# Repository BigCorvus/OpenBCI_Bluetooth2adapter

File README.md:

# OpenBCI_Bluetooth2adapter

Eagle files for an adapter board for the OpenBCI 32bit V3 board (Cyton) that enables higher data/sampling rates and eliminates the need for a USB dongle. Reliable operation is possible with 500Hz and 8 channels or 250Hz and 16 Channels. The OpenBCI GUI 2.0 is able to keep up with that.
The bluetooth module used is the common HC-05. Programming the board is still accomplished via dongle/RFduino.

In order for this board to work you have to implement WinslowStrong's changes in firmware (https://github.com/WinslowStrong/OpenBCI_Wired_USB) and you have to set up a baud rate of 230400baud on your bluetooth module (this is the highest rate I've been able to acheive reliably with the HC05). 
I've modified my Cyton board by putting the RFduino module on headers so that it can be removed after flashing the modified firmware. 

A solder jumper is included on the bottom side of the board to enter programming mode. You can short it temporarily using some metal object. In command mode (the LED is blinking slowly) you have to set a baud rate of 38400baud 8N1 and send after each command \r\n. If you enter AT the module should respond with OK.
To set the baud rate just enter AT+UART=230400,0,0 and to set the name type in AT+NAME=OpenBCI32 or whatever name you like. 

Edit: I also created a version for the RN42 module (http://www.digikey.com/product-detail/en/microchip-technology/RN42-I-RM630/RN42-I-RM630-ND/6009311) which can acheive speeds at up to 460800 baud in the system.

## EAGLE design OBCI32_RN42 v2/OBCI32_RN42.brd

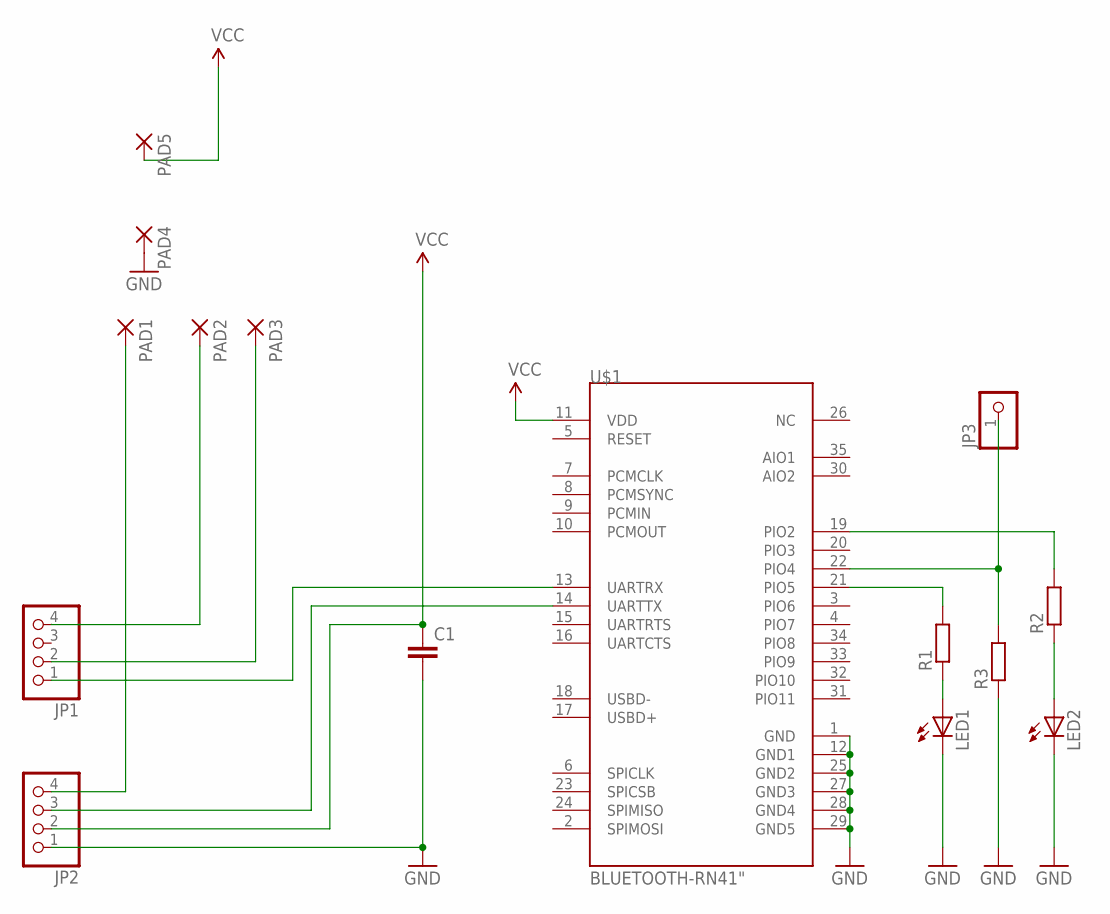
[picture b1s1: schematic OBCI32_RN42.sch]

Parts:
C1: C-EUC0805; C0805
JP1, JP2: PINHD-1X4; 1X04
JP3: PINHD-1X1; 1X01
LED1, LED2: LEDCHIP-LED0805; CHIP-LED0805
PAD1, PAD2, PAD3, PAD4, PAD5: SMD2; SMD1,27-2,54
R1, R2, R3: R-EU_R0603; R0603
U$1: BLUETOOTH-RN41"; RN41

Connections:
GND: C1.2, JP2.1, LED1.C, LED2.C, PAD4.1, R3.1, U$1.1 (GND), U$1.12 (GND1), U$1.25 (GND2), U$1.27 (GND3), U$1.28 (GND4), U$1.29 (GND5)
unnamed: R1.2, U$1.21 (PIO5)
unnamed: R2.2, U$1.19 (PIO2)
unnamed: JP2.3, U$1.14 (UARTTX)
unnamed: JP1.1, U$1.13 (UARTRX)
unnamed: LED1.A, R1.1
unnamed: JP1.2, PAD3.1
unnamed: JP1.4, PAD2.1
unnamed: JP2.4, PAD1.1
unnamed: LED2.A, R2.1
unnamed: JP3.1, R3.2, U$1.22 (PIO4)
VCC: C1.1, JP2.2, PAD5.1, U$1.11 (VDD)

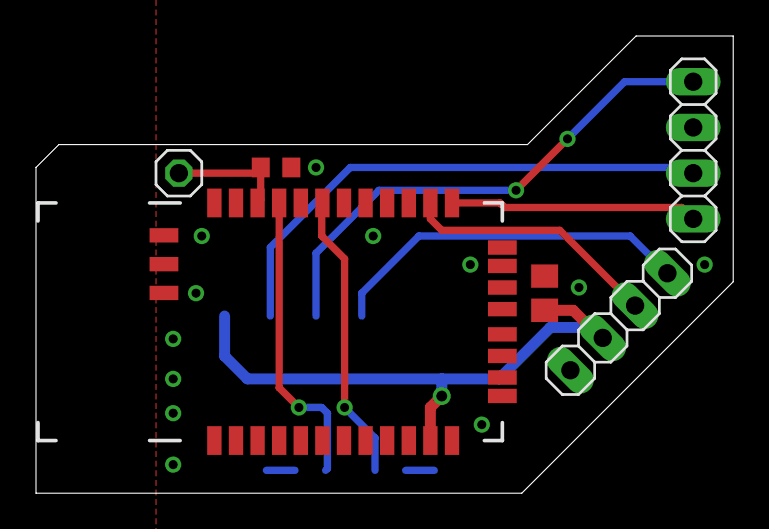
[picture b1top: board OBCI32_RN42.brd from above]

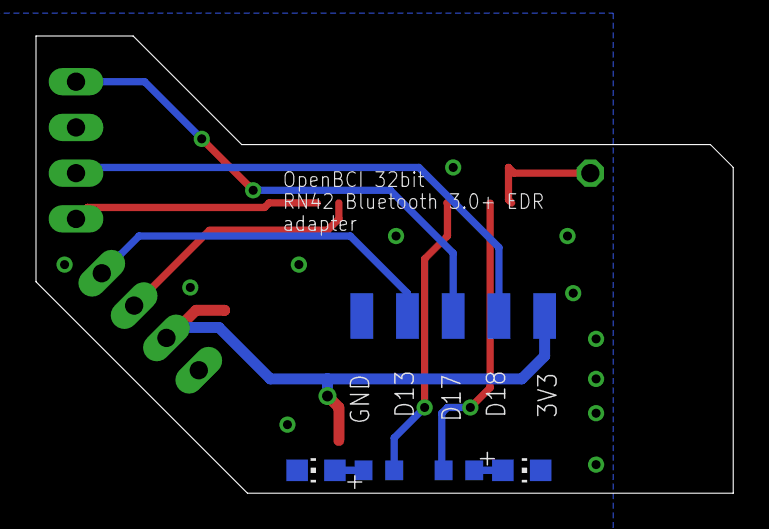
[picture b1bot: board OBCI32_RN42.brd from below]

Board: 2 copper layers, 38.7 x 25.4 mm, 15 parts (9 on the bottom side), 12 nets.

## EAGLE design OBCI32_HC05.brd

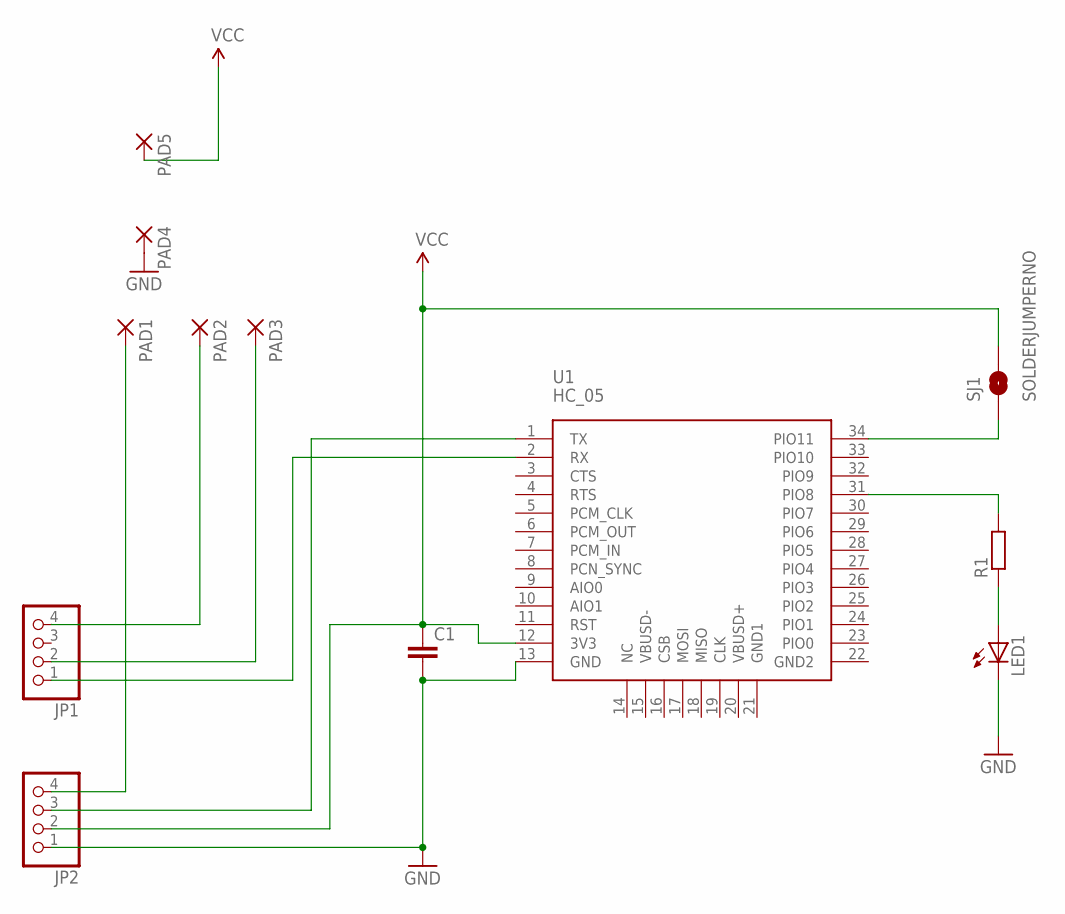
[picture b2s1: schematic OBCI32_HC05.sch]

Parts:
C1: C-EUC0805; C0805
JP1, JP2: PINHD-1X4; 1X04
LED1: LEDCHIP-LED0805; CHIP-LED0805
PAD1, PAD2, PAD3, PAD4, PAD5: SMD2; SMD1,27-2,54
R1: R-EU_R0603; R0603
SJ1: SOLDERJUMPERNO; SJ_2S-NO
U1: HC_05; BLUETOOTH_SMD

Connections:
GND: C1.2, JP2.1, LED1.C, PAD4.1, U1.13 (GND)
unnamed: LED1.A, R1.1
unnamed: JP2.3, U1.1 (TX)
unnamed: JP1.1, U1.2 (RX)
unnamed: R1.2, U1.31 (PIO8)
unnamed: SJ1.1, U1.34 (PIO11)
unnamed: JP1.2, PAD3.1
unnamed: JP1.4, PAD2.1
unnamed: JP2.4, PAD1.1
VCC: C1.1, JP2.2, PAD5.1, SJ1.2, U1.12 (3V3)

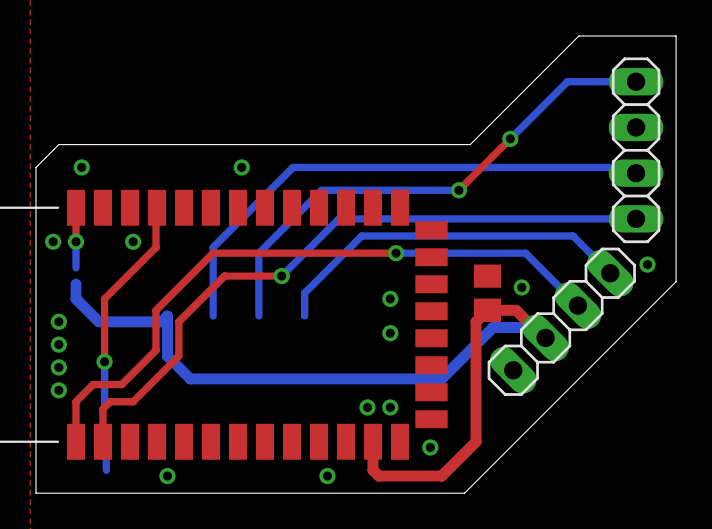
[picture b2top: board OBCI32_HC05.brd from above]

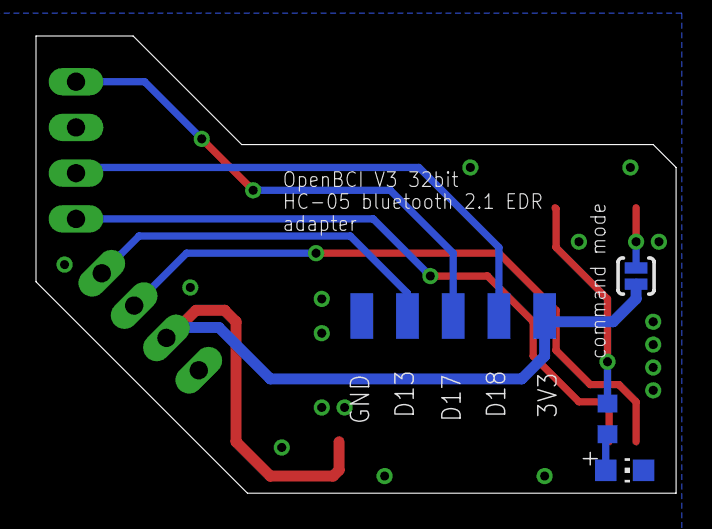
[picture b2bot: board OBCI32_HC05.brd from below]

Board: 2 copper layers, 35.6 x 25.4 mm, 12 parts (8 on the bottom side), 10 nets.

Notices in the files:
parts and their libraries:
SparkFun-Retired: Licensing:Creative Commons ShareAlike 4.0 International - https://creativecommons.org/licenses/by-sa/4.0
